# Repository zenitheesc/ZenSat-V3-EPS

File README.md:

<h1 align="center" style="color:white; background-color:black">ZenSat V3</h1>
<h4 align="center">Projeto de um CubeSat 2U para a competição Cube Design</h4>

<p align="center">

</p>

<p align="center">
    <a href="#environment-and-tools">Environment and Tools</a> •
    <a href="#steps-to-run-and-debug">Steps to run and debug</a> •
    <a href="#how-to-contribute">How to contribute?</a> •
</p>

## Environment and tools

`Add list of dependencies and software needed to run this project (if possible add the versions that were used in development).`

## Steps to run and debug

`A simple list of steps indicating how one can run and test the project.`

## How to contribute

`(optional, depends on the project) list of simple rules to help people work on the project.`

`Examples: How to format a pull request\n How to format an issue`

---

<p align="center">

</p>
<p align = "center">
<a href="zenith.eesc@gmail.com">zenith.eesc@gmail.com</a>
</p>

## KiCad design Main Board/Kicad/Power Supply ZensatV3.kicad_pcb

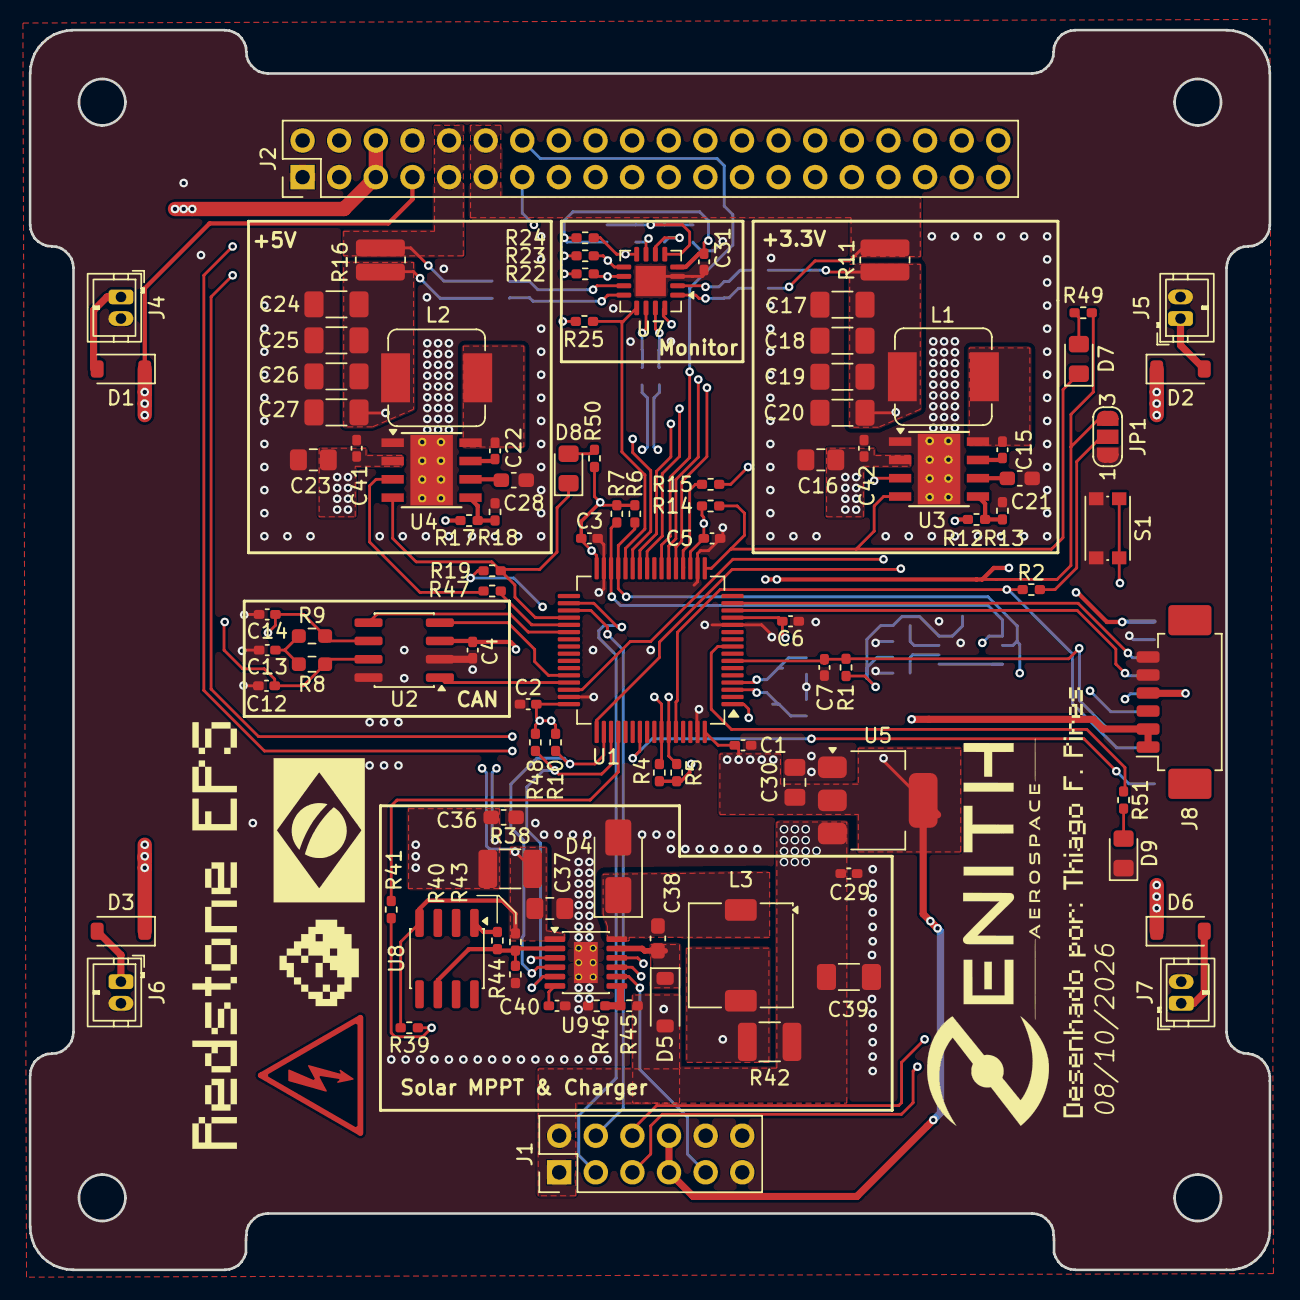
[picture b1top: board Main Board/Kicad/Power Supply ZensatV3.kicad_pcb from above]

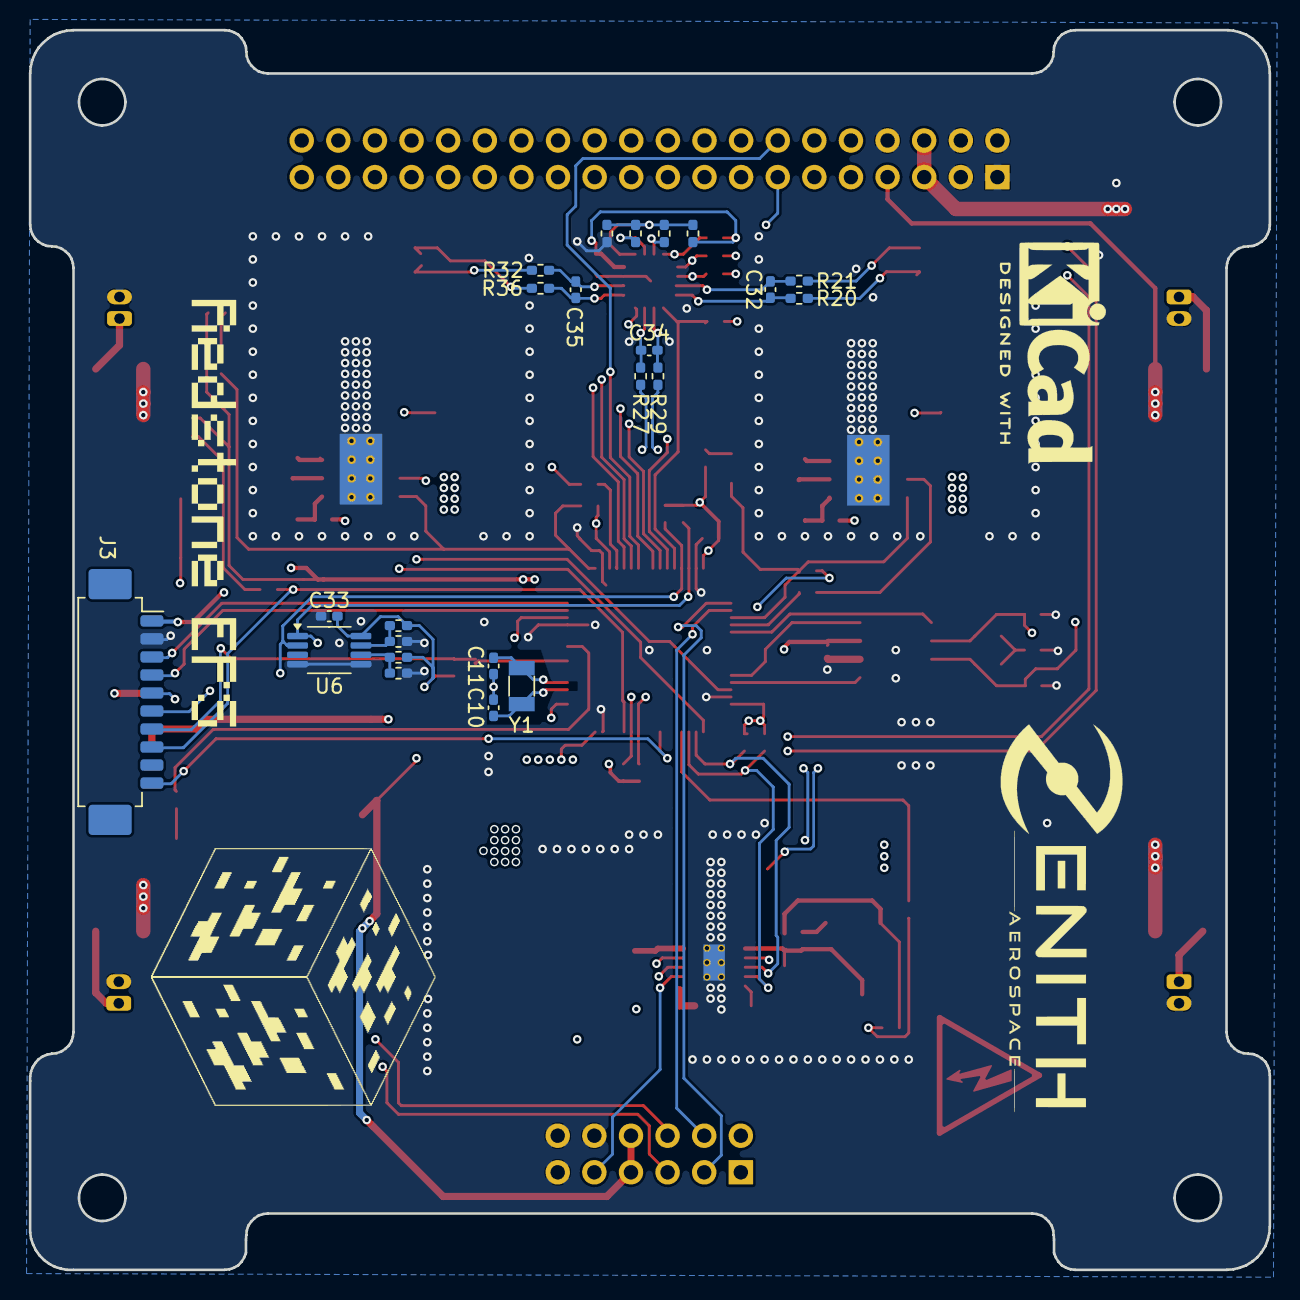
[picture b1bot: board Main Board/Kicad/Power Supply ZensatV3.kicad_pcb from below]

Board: 4 copper layers, 86.0 x 86.0 mm, 122 parts (23 on the bottom side), 81 nets.

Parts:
C1, C2, C3, C4, C5, C6, C15, C22, C33: 100nF; C_0402_1005Metric_Pad0.74x0.62mm_HandSolder
C7: 1u; C_0402_1005Metric_Pad0.74x0.62mm_HandSolder
C10, C11: 7p; C_0402_1005Metric_Pad0.74x0.62mm_HandSolder
C12, C14: 33p; C_0402_1005Metric_Pad0.74x0.62mm_HandSolder
C13: 4n7; C_0402_1005Metric_Pad0.74x0.62mm_HandSolder
C16, C23, C37: 10uF; C_0805_2012Metric_Pad1.18x1.45mm_HandSolder
C17, C18, C19, C20, C24, C25, C26, C27: 22uF; C_1206_3216Metric_Pad1.33x1.80mm_HandSolder
C21, C28, C36: 1uF; C_0603_1608Metric_Pad1.08x0.95mm_HandSolder
C29: 100nF 25V; C_0402_1005Metric_Pad0.74x0.62mm_HandSolder
C30: 10uF 10V; C_0805_2012Metric_Pad1.18x1.45mm_HandSolder
C31, C32, C34, C35: 100nF 10V; C_0402_1005Metric_Pad0.74x0.62mm_HandSolder
C38: 1uF 50V; C_0603_1608Metric_Pad1.08x0.95mm_HandSolder
C39: 10uF 25V; C_1206_3216Metric_Pad1.33x1.80mm_HandSolder
C40: 680nF; C_0402_1005Metric_Pad0.74x0.62mm_HandSolder
C41, C42: 220nF; C_0402_1005Metric_Pad0.74x0.62mm_HandSolder
D1, D2, D3, D5, D6: 1N5819HW; D_SOD-123
D4: SS34; D_SMA
D7, D8: LEDG; LED_0805_2012Metric_Pad1.15x1.40mm_HandSolder
D9: LEDR; LED_0805_2012Metric_Pad1.15x1.40mm_HandSolder
J1: BatBus; PinHeader_2x06_P2.54mm_Vertical
J2: ZenBus; PinHeader_2x20_P2.54mm_Vertical
J3: Programmer; Molex_PicoBlade_53261-1071_1x10-1MP_P1.25mm_Horizontal
J4, J5, J6, J7: Conn_01x02_Pin; JST_ZH_B2B-ZR_1x02_P1.50mm_Vertical
J8: External Power; Molex_PicoBlade_53261-0671_1x06-1MP_P1.25mm_Horizontal
JP1: BOOT; SolderJumper-3_P1.3mm_Open_RoundedPad1.0x1.5mm_NumberLabels
L1: 6,8uH; L_Sumida_CDMC6D28_7.25x6.5mm
L2: 8uH; L_Sumida_CDMC6D28_7.25x6.5mm
L3: 47uH; L_TDK_SLF7032
R1, R2, R4, R5, R10, R14, R19, R22, R23, R24, R25, R48, R51: 10k; R_0402_1005Metric_Pad0.72x0.64mm_HandSolder
R6, R7: 4k7; R_0402_1005Metric_Pad0.72x0.64mm_HandSolder
R8, R9: 60; R_0603_1608Metric_Pad0.98x0.95mm_HandSolder
R11, R16: R05; R_0612_1632Metric_Pad1.18x3.40mm_HandSolder
R12, R17: 100k; R_0402_1005Metric_Pad0.72x0.64mm_HandSolder
R13: 43,2k; R_0402_1005Metric_Pad0.72x0.64mm_HandSolder
R15, R43, R47: 1k; R_0402_1005Metric_Pad0.72x0.64mm_HandSolder
R18: 14,9k; R_0402_1005Metric_Pad0.72x0.64mm_HandSolder
R20, R21, R27, R29, R32, R36: 10R; R_0402_1005Metric_Pad0.72x0.64mm_HandSolder
R26, R28, R30, R31, R33, R34, R35, R37, R39, R41: 0R; R_0402_1005Metric_Pad0.72x0.64mm_HandSolder
R38, R42: 0R33; R_1210_3225Metric_Pad1.30x2.65mm_HandSolder
R40: 233k; R_0402_1005Metric_Pad0.72x0.64mm_HandSolder
R44: 25,2k; R_0402_1005Metric_Pad0.72x0.64mm_HandSolder
R45: 626k; R_0402_1005Metric_Pad0.72x0.64mm_HandSolder
R46: 412k; R_0402_1005Metric_Pad0.72x0.64mm_HandSolder
R49, R50: 470R; R_0402_1005Metric_Pad0.72x0.64mm_HandSolder
S1: RST; SW_Push_1P1T_NO_CK_KMR2
U1: STM32L476RGTx; LQFP-64_10x10mm_P0.5mm
U2: SN65HVD233; SOIC-8_3.9x4.9mm_P1.27mm
U3, U4: LMR33630ADDA; Texas_HSOP-8-1EP_3.9x4.9mm_P1.27mm_ThermalVias
U5: AMS1117-3.3; SOT-223-3_TabPin2
U6: LM75B; Texas_S-PDSO-G8_3x3mm_P0.65mm
U7: INA3221; Texas_RGV0016A_VQFN-16-1EP_4x4mm_P0.65mm_EP2.1x2.1mm
U8: LM234DT; SOIC-8_3.9x4.9mm_P1.27mm
U9: LT3652IMSE; MSOP-12-1EP_3x4.039mm_P0.65mm_EP1.651x2.845mm_ThermalVias
Y1: 32,768k; Crystal_SMD_3215-2Pin_3.2x1.5mm

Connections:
+3.3VP: C1.2, C2.2, C3.2, C4.2, C5.2, C6.2, C30.2, C31.2, C33.2, J1.7, J1.8, J3.1, JP1.3 (B), R1.1, R4.1, R5.1, R6.1, R7.1, R10.1, R14.1, R19.1, R22.2, R23.2, R24.2, R25.2, R26.1, R30.1, R31.1, R48.1, R49.1, R50.1, U1.1 (VBAT), U1.13 (VDDA), U1.19 (VDD), U1.32 (VDD), U1.48 (VDDUSB), U1.64 (VDD), U2.3 (VCC), U5.2 (VO), U6.8 (+Vs), U7.4 (VS), U7.16 (VPU)
+3V3: J2.11, J2.12, R11.2, R36.2
+3V3_Sense: C17.2, C18.2, C19.2, C20.2, L1.2, R11.1, R12.1, R32.2
+5V: J2.9, J2.10, R16.2, R21.2
+5V_Sense: C24.2, C25.2, C26.2, C27.2, L2.2, R16.1, R17.1, R20.2
/+3V3_En: R15.1, U1.20 (PA4)
/+3V3_PG: D7.1 (K), R14.2, U1.17 (PA3), U3.4 (PG)
/+5V_En: R47.1, U1.37 (PC6)
/+5V_PG: D8.1 (K), R19.2, U1.36 (PB15), U4.4 (PG)
/BOOT0: J3.8, R2.1, U1.60 (BOOT0)
/BUS_CAN+: C12.2, J2.16, R8.1, U2.7 (CANH)
/BUS_CAN-: C14.1, J2.18, R9.2, U2.6 (CANL)
/BUS_I2C_SCL: J2.19, R4.2, U1.58 (PB6)
/BUS_I2C_SDA: J2.17, R5.2, U1.59 (PB7)
/CAN_Rx: U1.44 (PA11), U2.4 (R)
/CAN_Tx: U1.45 (PA12), U2.1 (D)
/CRITICAL: R23.1, U1.26 (PB0), U7.9 (CRITICAL)
/DebugLed: R51.1, U1.9 (PC1)
/Deploy: J1.4, U1.35 (PB14)
/Heater: J1.3, U1.34 (PB13)
/I2C2_SCL: J1.5, R6.2, R35.1, U1.29 (PB10), U6.2 (SCL), U7.6 (SCL)
/I2C2_SDA: J1.6, R7.2, R33.1, U1.30 (PB11), U6.1 (SDA), U7.7 (SDA)
/LBK: U1.38 (PC7), U2.5 (LBK)
/NRST: C7.1, J3.7, R1.2, S1.1, U1.7 (NRST)
/NTC: J1.9, U9.8 (NTC)
/OSC32_IN: C10.1, U1.3 (PC14), Y1.2
/OSC32_OUT: C11.2, U1.4 (PC15), Y1.1
/PV: R22.1, U1.25 (PC5), U7.10 (PV)
/SPI1_MISO: J2.13, U1.22 (PA6)
/SPI1_MOSI: J2.14, U1.23 (PA7)
/SPI1_SCK: J2.15, U1.21 (PA5)
/SWCLK: J3.5, U1.49 (PA14)
/SWDIO: J3.6, U1.46 (PA13)
/SWO: J3.10, U1.55 (PB3)
/TC: R25.1, U1.28 (PB2), U7.13 (TC)
/UART_Rx: J3.3, U1.15 (PA1)
/UART_Tx: J3.4, U1.14 (PA0)
/WARNING: R24.1, U1.27 (PB1), U7.8 (WARNING)
/~CHRG: R10.2, U1.50 (PA15), U9.4 (~CHRG)
/~FAULT: R48.2, U1.51 (PC10), U9.5 (~FAULT)
/~SHDN: R41.1, U1.52 (PC11)
BAT+: C16.2, C23.2, C29.2, C39.1, C41.2, C42.2, D5.2 (A), J1.1, J1.2, J2.5, J2.6, J8.1, J8.2, R42.2, R45.2, U3.2 (VIN), U4.2 (VIN), U5.3 (VI), U9.9 (BAT)
GND: C1.1, C2.1, C3.1, C4.1, C5.1, C6.1, C7.2, C10.2, C11.1, C12.1, C13.2, C14.2, C16.1, C17.1, C18.1, C19.1, C20.1, C21.1, C23.1, C24.1, C25.1, C26.1, C27.1, C28.1, C29.1, C30.1, C31.1, C33.1, C36.1, C37.2, C39.2, C40.2, C41.1, C42.1, D4.2 (A), D9.1 (K), J1.10, J1.11, J1.12, J2.1, J2.2, J2.3, J2.4, J2.8, J3.2, J4.2, J5.2, J6.2, J7.2, J8.5, J8.6, JP1.1 (A), R13.2, R18.2, R28.1, R34.1, R37.1, R44.1, R46.1, S1.2, U1.12 (VSSA), U1.18 (VSS), U1.31 (VSS), U1.47 (VSS), U1.63 (VSS), U2.2 (GND), U2.8 (Rs), U3.1 (GND), U3.9 (GND), U4.1 (GND), U4.9 (GND), U5.1 (GND), U6.4 (GND), U6.5 (A2), U7.3 (GND), U7.17 (EP), U9.13 (GND)
unnamed: C13.1, R8.2, R9.1
unnamed: D1.2 (A), J4.1
unnamed: D2.2 (A), J5.1
unnamed: D3.2 (A), J6.1
unnamed: C38.1, D4.1 (K), L3.1, U9.12 (SW)
unnamed: C38.2, D5.1 (K), U9.11 (BOOST)
unnamed: D6.2 (A), J7.1
unnamed: D7.2 (A), R49.2
unnamed: D8.2 (A), R50.2
unnamed: D9.2 (A), R51.2
unnamed: JP1.2 (C), R2.2
unnamed: R43.2, U8.1
unnamed: C15.1, U3.7 (BOOT)
unnamed: R15.2, U3.3 (EN)
unnamed: R12.2, R13.1, U3.5 (FB)
unnamed: C15.2, L1.1, U3.8 (SW)
unnamed: C21.2, U3.6 (VCC)
unnamed: C22.1, U4.7 (BOOT)
unnamed: R47.2, U4.3 (EN)
unnamed: R17.2, R18.1, U4.5 (FB)
unnamed: C22.2, L2.1, U4.8 (SW)
unnamed: C28.2, U4.6 (VCC)
unnamed: R26.2, R28.2, U6.7 (A0)
unnamed: R31.2, R34.2, U6.6 (A1)
unnamed: R30.2, R33.2, R35.2, R37.2, U7.5 (A0)
unnamed: C32.1, R20.1, U7.12 (IN+1)
unnamed: C34.1, R27.1, U7.15 (IN+2)
unnamed: C35.1, R32.1, U7.2 (IN+3)
unnamed: C32.2, R21.1, U7.11 (IN-1)
unnamed: C34.2, R29.1, U7.14 (IN-2)
unnamed: C35.2, R36.1, U7.1 (IN-3)
unnamed: L3.2, R42.1, U9.10 (SENSE)
unnamed: C40.1, U9.6 (TIMER)
unnamed: R45.1, R46.2, U9.7 (V_{FB})
unnamed: R40.1, R43.1, R44.2, U8.6, U9.2 (V_{IN_REG})
unnamed: R39.1, R41.2, U9.3 (~SHDN)
SOL+: C36.2, D1.1 (K), D2.1 (K), D3.1 (K), D6.1 (K), J2.7, J8.4, R27.2, R38.1
SOL_Sense-: C37.1, R29.2, R38.2, R39.2, R40.2, U8.4, U9.1 (V_{IN})

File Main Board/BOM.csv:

"Reference","Qty","Value","DNP","Exclude from BOM","Exclude from Board","Footprint"
"C1,C2,C3,C4,C5,C6,C15,C22,C33","9","100nF","","","","Capacitor_SMD:C_0402_1005Metric_Pad0.74x0.62mm_HandSolder"
"C7","1","1u","","","","Capacitor_SMD:C_0402_1005Metric_Pad0.74x0.62mm_HandSolder"
"C10,C11","2","7p","","","","Capacitor_SMD:C_0402_1005Metric_Pad0.74x0.62mm_HandSolder"
"C12,C14","2","33p","","","","Capacitor_SMD:C_0402_1005Metric_Pad0.74x0.62mm_HandSolder"
"C13","1","4n7","","","","Capacitor_SMD:C_0402_1005Metric_Pad0.74x0.62mm_HandSolder"
"C16,C23,C37","3","10uF","","","","Capacitor_SMD:C_0805_2012Metric_Pad1.18x1.45mm_HandSolder"
"C17,C18,C19,C20,C24,C25,C26,C27","8","22uF","","","","Capacitor_SMD:C_1206_3216Metric_Pad1.33x1.80mm_HandSolder"
"C21,C28,C36","3","1uF","","","","Capacitor_SMD:C_0603_1608Metric_Pad1.08x0.95mm_HandSolder"
"C29","1","100nF 25V","","","","Capacitor_SMD:C_0402_1005Metric_Pad0.74x0.62mm_HandSolder"
"C30","1","10uF 10V","","","","Capacitor_SMD:C_0805_2012Metric_Pad1.18x1.45mm_HandSolder"
"C31,C32,C34,C35","4","100nF 10V","","","","Capacitor_SMD:C_0402_1005Metric_Pad0.74x0.62mm_HandSolder"
"C38","1","1uF 50V","","","","Capacitor_SMD:C_0603_1608Metric_Pad1.08x0.95mm_HandSolder"
"C39","1","10uF 25V","","","","Capacitor_SMD:C_1206_3216Metric_Pad1.33x1.80mm_HandSolder"
"C40","1","680nF","","","","Capacitor_SMD:C_0402_1005Metric_Pad0.74x0.62mm_HandSolder"
"C41,C42","2","220nF","","","","Capacitor_SMD:C_0402_1005Metric_Pad0.74x0.62mm_HandSolder"
"D1,D2,D3,D5,D6","5","1N5819HW","","","","Diode_SMD:D_SOD-123"
"D4","1","SS34","","","","Diode_SMD:D_SMA"
"D7,D8","2","LEDG","","","","LED_SMD:LED_0805_2012Metric_Pad1.15x1.40mm_HandSolder"
"D9","1","LEDR","","","","LED_SMD:LED_0805_2012Metric_Pad1.15x1.40mm_HandSolder"
"J1","1","BatBus","","","","Connector_PinHeader_2.54mm:PinHeader_2x06_P2.54mm_Vertical"
"J2","1","ZenBus","","","","Connector_PinHeader_2.54mm:PinHeader_2x20_P2.54mm_Vertical"
"J3","1","Programmer","","","","Connector_Molex:Molex_PicoBlade_53261-1071_1x10-1MP_P1.25mm_Horizontal"
"J4,J5,J6,J7","4","Conn_01x02_Pin","","","","Connector_JST:JST_ZH_B2B-ZR_1x02_P1.50mm_Vertical"
"J8","1","External Power","","","","Connector_Molex:Molex_PicoBlade_53261-0671_1x06-1MP_P1.25mm_Horizontal"
"JP1","1","BOOT","","","","Jumper:SolderJumper-3_P1.3mm_Open_RoundedPad1.0x1.5mm_NumberLabels"
"L1","1","6,8uH","","","","Inductor_SMD:L_Sumida_CDMC6D28_7.25x6.5mm"
"L2","1","8uH","","","","Inductor_SMD:L_Sumida_CDMC6D28_7.25x6.5mm"
"L3","1","47uH","","","","Inductor_SMD:L_TDK_SLF7032"
"R1,R2,R4,R5,R10,R14,R19,R22,R23,R24,R25,R48,R51","13","10k","","","","Resistor_SMD:R_0402_1005Metric_Pad0.72x0.64mm_HandSolder"
"R6,R7","2","4k7","","","","Resistor_SMD:R_0402_1005Metric_Pad0.72x0.64mm_HandSolder"
"R8,R9","2","60","","","","Resistor_SMD:R_0603_1608Metric_Pad0.98x0.95mm_HandSolder"
"R11,R16","2","R05","","","","Resistor_SMD:R_0612_1632Metric_Pad1.18x3.40mm_HandSolder"
"R12,R17","2","100k","","","","Resistor_SMD:R_0402_1005Metric_Pad0.72x0.64mm_HandSolder"
"R13","1","43,2k","","","","Resistor_SMD:R_0402_1005Metric_Pad0.72x0.64mm_HandSolder"
"R15,R43,R47","3","1k","","","","Resistor_SMD:R_0402_1005Metric_Pad0.72x0.64mm_HandSolder"
"R18","1","14,9k","","","","Resistor_SMD:R_0402_1005Metric_Pad0.72x0.64mm_HandSolder"
"R28,R33,R34,R35,R37,R39,R41","7","0R","","","","Resistor_SMD:R_0402_1005Metric_Pad0.72x0.64mm_HandSolder"
"R38,R42","2","0R33","","","","Resistor_SMD:R_1210_3225Metric_Pad1.30x2.65mm_HandSolder"
"R40","1","233k","","","","Resistor_SMD:R_0402_1005Metric_Pad0.72x0.64mm_HandSolder"
"R44","1","25,2k","","","","Resistor_SMD:R_0402_1005Metric_Pad0.72x0.64mm_HandSolder"
"R45","1","626k","","","","Resistor_SMD:R_0402_1005Metric_Pad0.72x0.64mm_HandSolder"
"R46","1","412k","","","","Resistor_SMD:R_0402_1005Metric_Pad0.72x0.64mm_HandSolder"
"R49,R50","2","470R","","","","Resistor_SMD:R_0402_1005Metric_Pad0.72x0.64mm_HandSolder"
"S1","1","RST","","","","Button_Switch_SMD:SW_Push_1P1T_NO_CK_KMR2"
"U1","1","STM32L476RGTx","","","","Package_QFP:LQFP-64_10x10mm_P0.5mm"
"U2","1","SN65HVD233","","","","Package_SO:SOIC-8_3.9x4.9mm_P1.27mm"
"U3,U4","2","LMR33630ADDA","","","","Package_SO:Texas_HSOP-8-1EP_3.9x4.9mm_P1.27mm_ThermalVias"
"U5","1","AMS1117-3.3","","","","Package_TO_SOT_SMD:SOT-223-3_TabPin2"
"U6","1","LM75B","","","","Package_SO:Texas_S-PDSO-G8_3x3mm_P0.65mm"
"U7","1","INA3221","","","","Package_DFN_QFN:Texas_RGV0016A_VQFN-16-1EP_4x4mm_P0.65mm_EP2.1x2.1mm"
"U8","1","LM234DT","","","","Package_SO:SOIC-8_3.9x4.9mm_P1.27mm"
"U9","1","LT3652IMSE","","","","Package_SO:MSOP-12-1EP_3x4.039mm_P0.65mm_EP1.651x2.845mm_ThermalVias"
"Y1","1","32,768k","","","","Crystal:Crystal_SMD_3215-2Pin_3.2x1.5mm"

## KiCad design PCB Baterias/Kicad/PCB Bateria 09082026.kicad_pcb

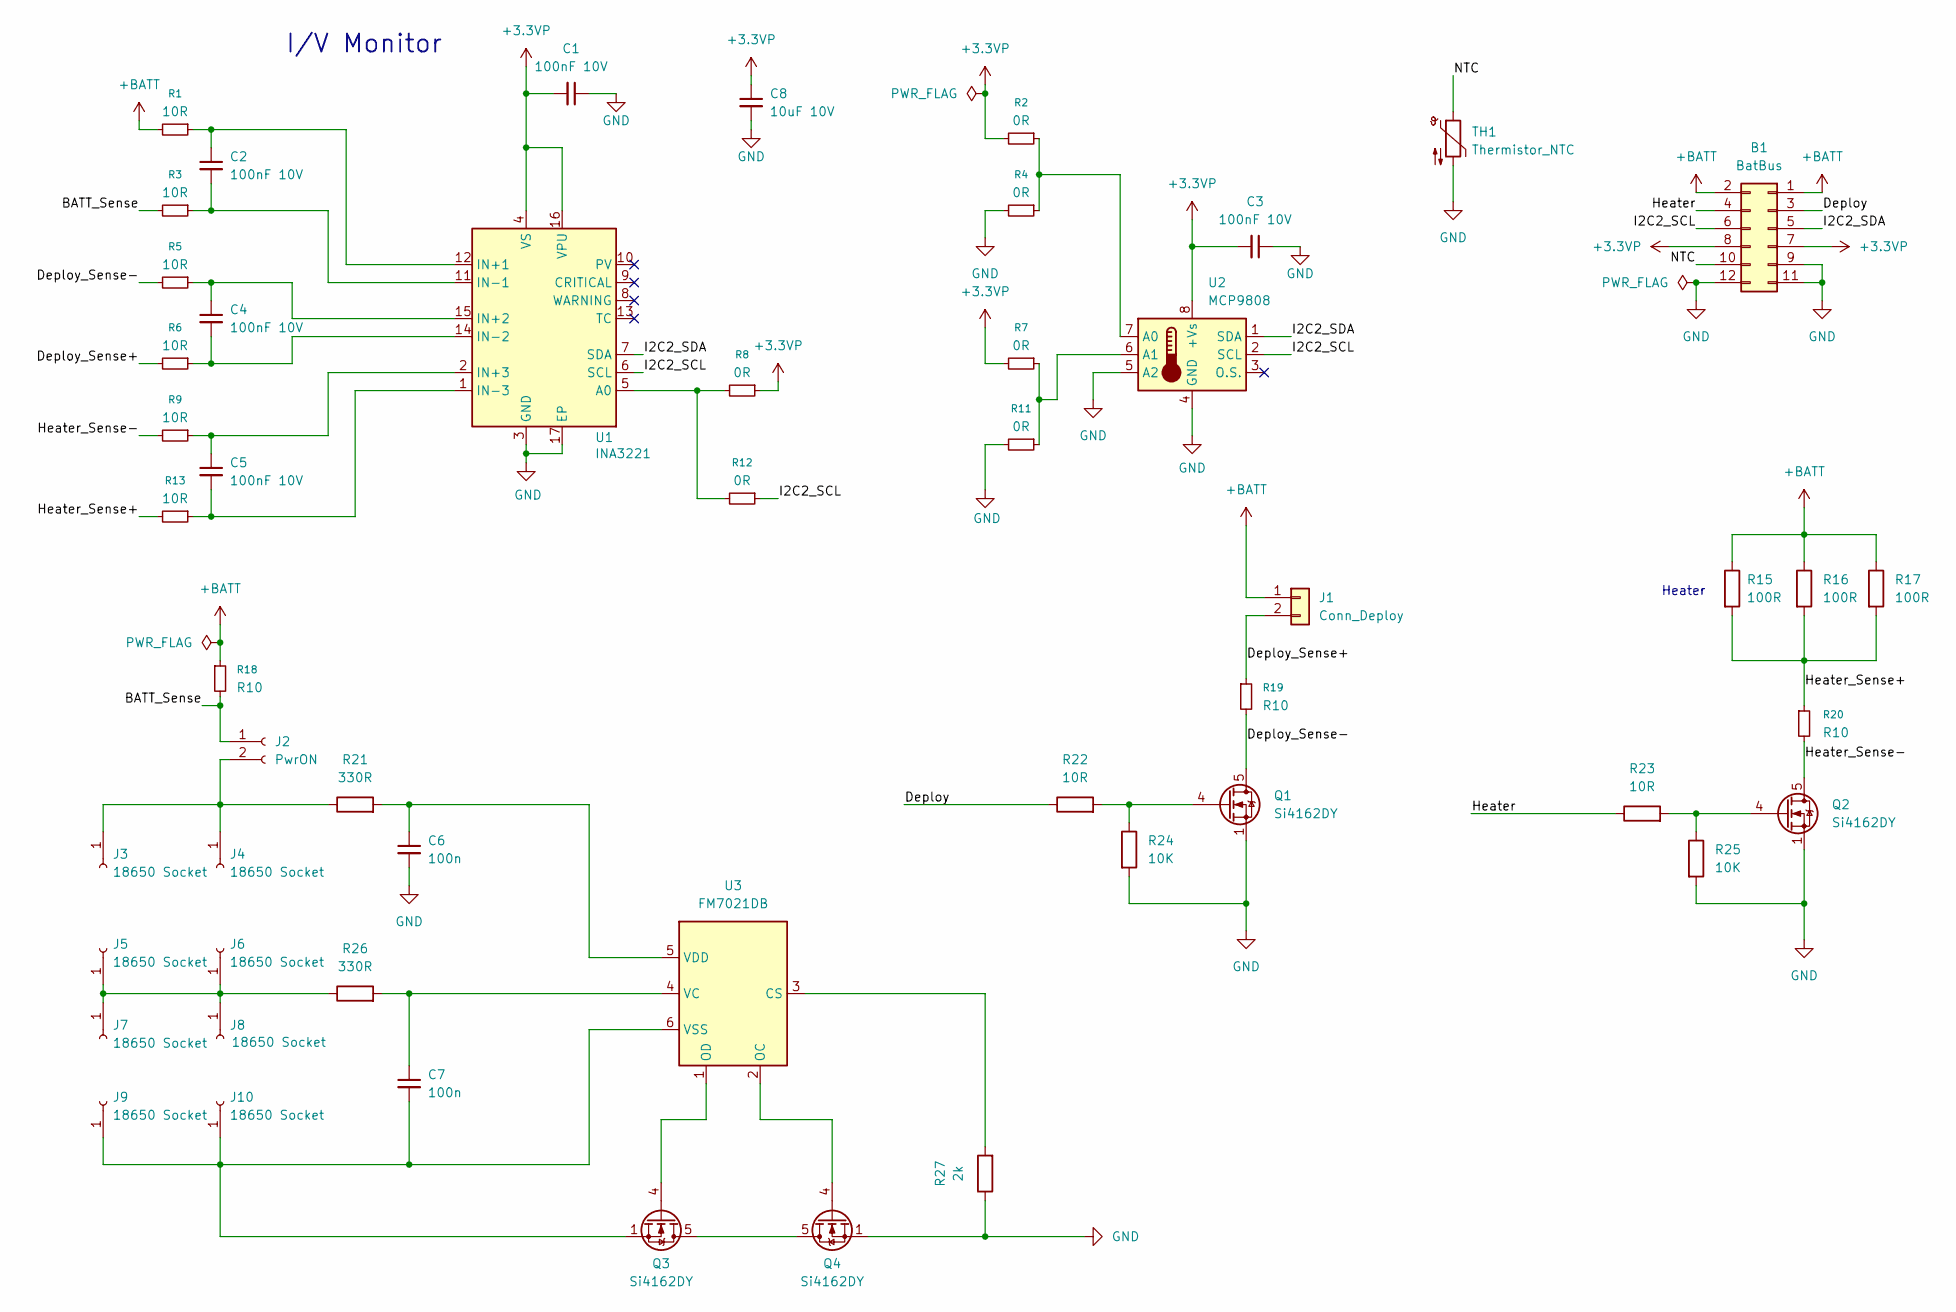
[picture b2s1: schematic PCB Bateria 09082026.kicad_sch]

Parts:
B1: BatBus; PinHeader_2x06_P2.54mm_Vertical_SMD
C1, C2, C3, C4, C5: 100nF 10V; C_0402_1005Metric_Pad0.74x0.62mm_HandSolder
C6, C7: 100n; C_0402_1005Metric_Pad0.74x0.62mm_HandSolder
C8: 10uF 10V; C_0805_2012Metric_Pad1.18x1.45mm_HandSolder
J1: Conn_Deploy; Molex_KK-254_AE-6410-02A_1x02_P2.54mm_Vertical
J2: PwrON; PinHeader_1x02_P2.54mm_Vertical
J3, J4, J5, J6, J7, J8, J9, J10: 18650 Socket; BatteryClip_Keystone_54_D16-19mm
Q1, Q2, Q3, Q4: Si4162DY; SOIC-8_3.9x4.9mm_P1.27mm
R1, R3, R5, R6, R9, R13, R22, R23: 10R; R_0402_1005Metric_Pad0.72x0.64mm_HandSolder
R2, R4, R7, R8, R11, R12: 0R; R_0402_1005Metric_Pad0.72x0.64mm_HandSolder
R15, R16, R17: 100R; R_Axial_DIN0516_L15.5mm_D5.0mm_P30.48mm_Horizontal
R18, R19, R20: R10; R_1206_3216Metric_Pad1.30x1.75mm_HandSolder
R21, R26: 330R; R_0402_1005Metric_Pad0.72x0.64mm_HandSolder
R24, R25: 10K; R_0402_1005Metric_Pad0.72x0.64mm_HandSolder
R27: 2k; R_0402_1005Metric_Pad0.72x0.64mm_HandSolder
TH1: Thermistor_NTC; R_Axial_DIN0204_L3.6mm_D1.6mm_P1.90mm_Vertical
U1: INA3221; Texas_RGV0016A_VQFN-16-1EP_4x4mm_P0.65mm_EP2.1x2.1mm
U2: MCP9808; MSOP-8_3x3mm_P0.65mm
U3: FM7021DB; SOT-23-6

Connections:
+3.3VP: B1.7, B1.8, C1.2, C3.2, C8.1, R2.2, R7.2, R8.1, U1.4 (VS), U1.16 (VPU), U2.8 (+Vs)
+BATT: B1.1, B1.2, J1.1, R1.2, R15.1, R16.1, R17.1, R18.1
/BATT_Sense: J2.1, R3.2, R18.2
/Deploy: B1.3, R22.1
/Deploy_Sense+: J1.2, R6.2, R19.1
/Deploy_Sense-: Q1.5 (D), Q1.6 (D), Q1.7 (D), Q1.8 (D), R5.2, R19.2
/Heater: B1.4, R23.1
/Heater_Sense+: R13.2, R15.2, R16.2, R17.2, R20.1
/Heater_Sense-: Q2.5 (D), Q2.6 (D), Q2.7 (D), Q2.8 (D), R9.2, R20.2
/I2C2_SCL: B1.6, R12.1, U1.6 (SCL), U2.2 (SCL)
/I2C2_SDA: B1.5, U1.7 (SDA), U2.1 (SDA)
/NTC: B1.10, TH1.1
GND: B1.9, B1.11, B1.12, C1.1, C3.1, C6.2, C8.2, Q1.1 (S), Q1.2 (S), Q1.3 (S), Q2.1 (S), Q2.2 (S), Q2.3 (S), Q4.1 (S), Q4.2 (S), Q4.3 (S), R4.2, R11.2, R24.2, R25.2, R27.1, TH1.2, U1.3 (GND), U1.17 (EP), U2.4 (GND), U2.5 (A2)
unnamed: J2.2, J3.1 (Pin_1_1), J4.1 (Pin_1_1), R21.1
unnamed: J5.1 (Pin_1_1), J6.1 (Pin_1_1), J7.1 (Pin_1_1), J8.1 (Pin_1_1), R26.1
unnamed: C7.2, J9.1 (Pin_1_1), J10.1 (Pin_1_1), Q3.1 (S), Q3.2 (S), Q3.3 (S), U3.6 (VSS)
unnamed: Q1.4 (G), R22.2, R24.1
unnamed: Q2.4 (G), R23.2, R25.1
unnamed: Q3.5 (D), Q3.6 (D), Q3.7 (D), Q3.8 (D), Q4.5 (D), Q4.6 (D), Q4.7 (D), Q4.8 (D)
unnamed: Q3.4 (G), U3.1 (OD)
unnamed: Q4.4 (G), U3.2 (OC)
unnamed: R8.2, R12.2, U1.5 (A0)
unnamed: C2.1, R1.1, U1.12 (IN+1)
unnamed: C4.1, R5.1, U1.15 (IN+2)
unnamed: C5.1, R9.1, U1.2 (IN+3)
unnamed: C2.2, R3.1, U1.11 (IN-1)
unnamed: C4.2, R6.1, U1.14 (IN-2)
unnamed: C5.2, R13.1, U1.1 (IN-3)
unnamed: R2.1, R4.1, U2.7 (A0)
unnamed: R7.1, R11.1, U2.6 (A1)
unnamed: R27.2, U3.3 (CS)
unnamed: C7.1, R26.2, U3.4 (VC)
unnamed: C6.1, R21.2, U3.5 (VDD)

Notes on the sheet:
Heater
I/V Monitor

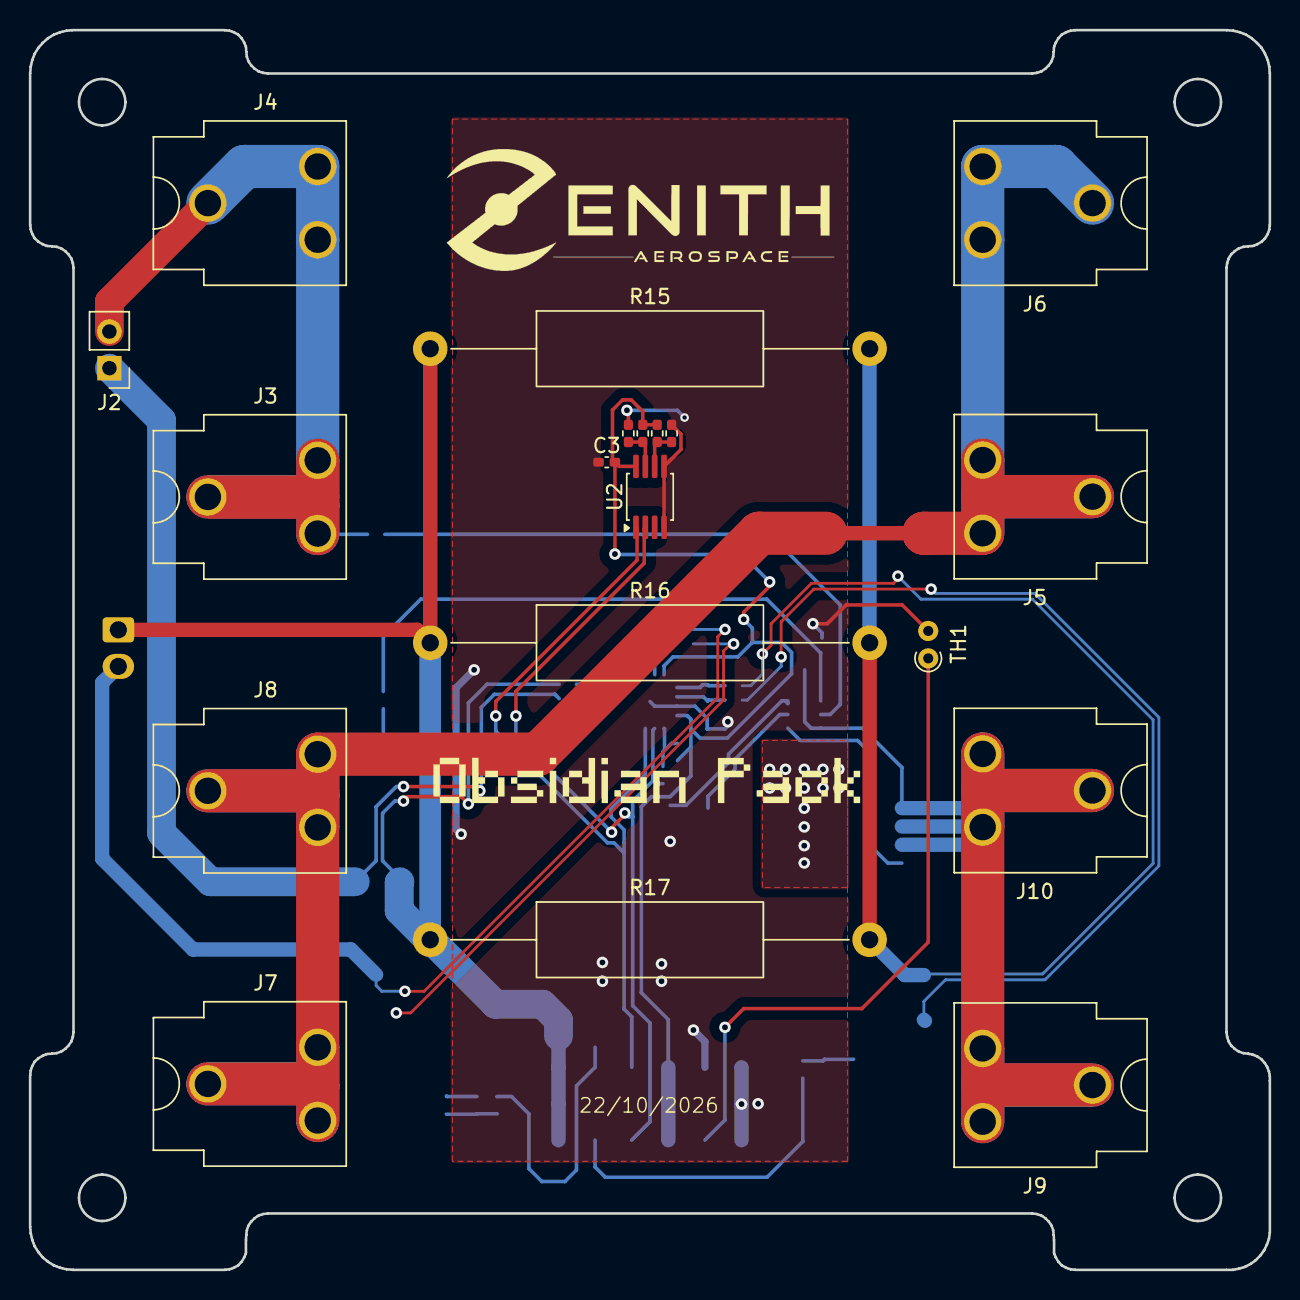
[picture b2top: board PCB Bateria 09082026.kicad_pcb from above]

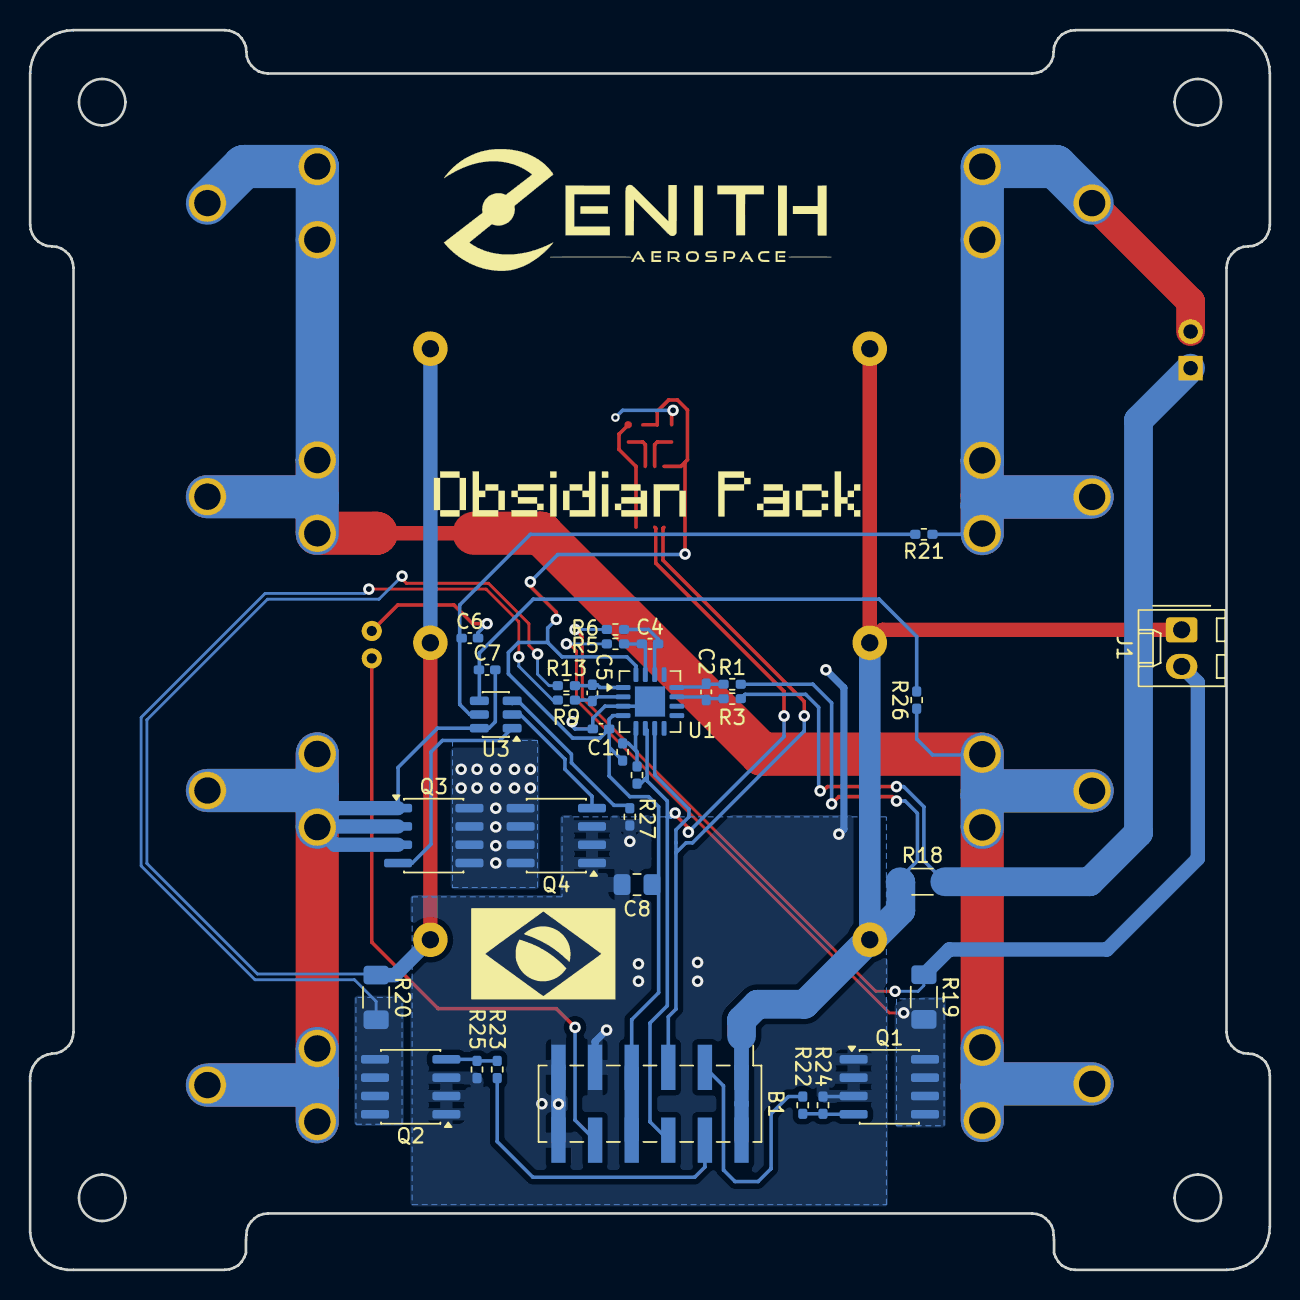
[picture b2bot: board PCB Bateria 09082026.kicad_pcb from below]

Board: 4 copper layers, 86.0 x 86.0 mm, 52 parts (33 on the bottom side), 33 nets.

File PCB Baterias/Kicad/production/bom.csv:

Designator,Footprint,Quantity,Value,LCSC Part #
B1,PinHeader_2x06_P2.54mm_Vertical_SMD,1,BatBus,
"C1, C2, C3, C4, C5",0402,5,100nF 10V,
"C6, C7",0402,2,100n,
C8,0805,1,10uF 10V,
J1,Molex_KK-254_AE-6410-02A_1x02_P2.54mm_Vertical,1,Conn_Deploy,
"J10, J3, J4, J5, J6, J7, J8, J9",BatteryClip_Keystone_54_D16-19mm,8,18650 Socket,
J2,PinHeader_1x02_P2.54mm_Vertical,1,PwrON,
"Q1, Q2, Q3, Q4",SOIC-8_3.9x4.9mm_P1.27mm,4,Si4162DY,
R12,0402,1,0R,
"R15, R16, R17",R_Axial_DIN0516_L15.5mm_D5.0mm_P30.48mm_Horizontal,3,100R,
"R21, R26",0402,2,330R,
"R22, R23",0402,2,10R,
"R24, R25",0402,2,10K,
R27,0402,1,2k,
TH1,R_Axial_DIN0204_L3.6mm_D1.6mm_P1.90mm_Vertical,1,Thermistor_NTC,
U1,Texas_RGV0016A_VQFN-16-1EP_4x4mm_P0.65mm_EP2.1x2.1mm,1,INA3221,
U2,MSOP-8_3x3mm_P0.65mm,1,MCP9808,
U3,SOT-23-6,1,FM7021DB,

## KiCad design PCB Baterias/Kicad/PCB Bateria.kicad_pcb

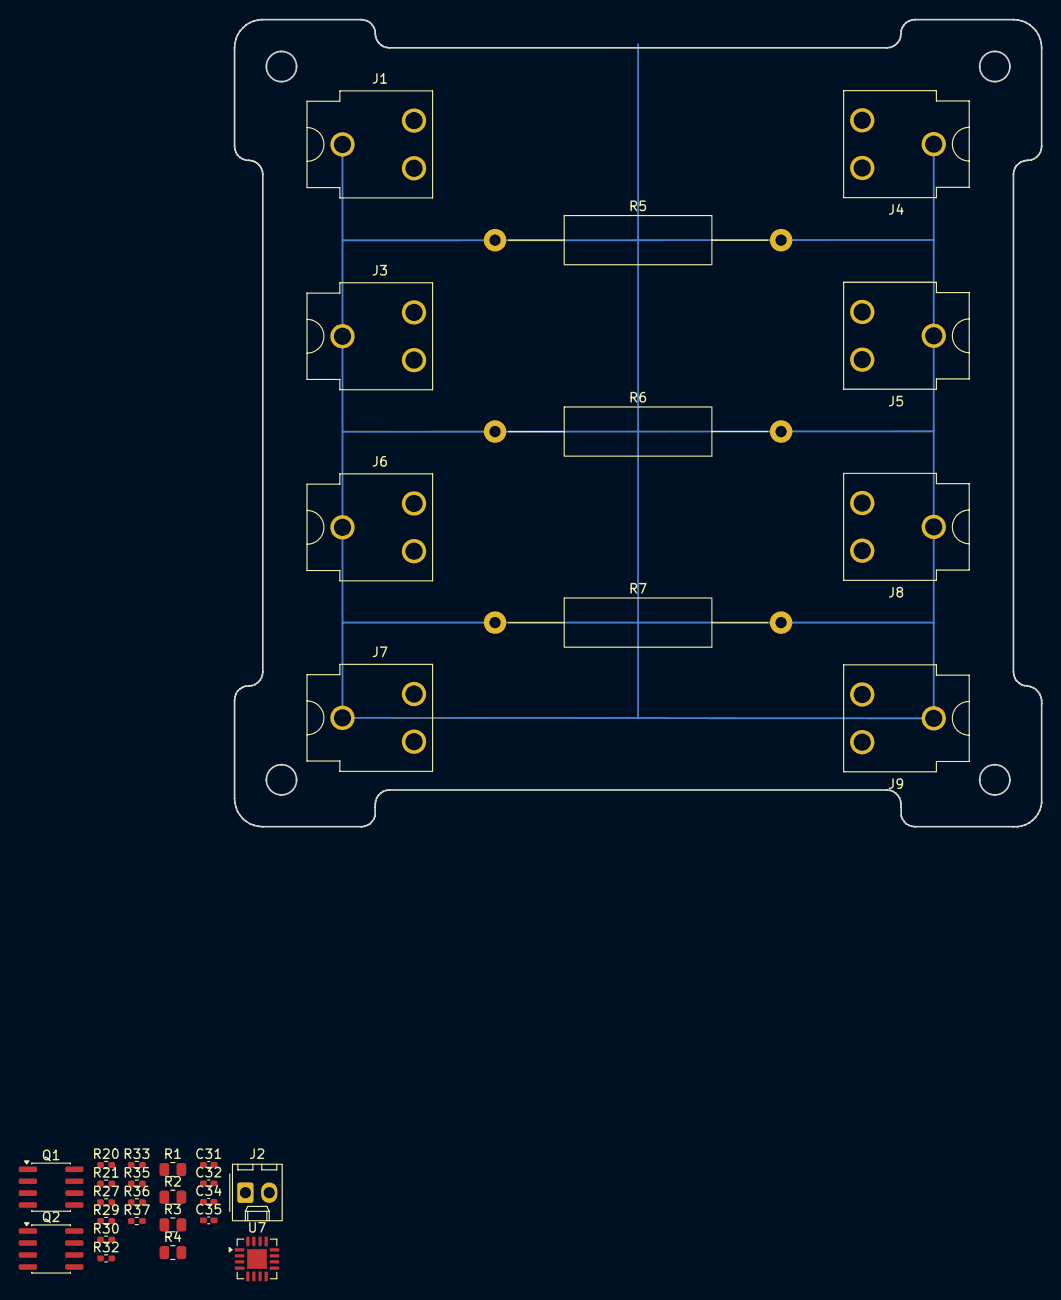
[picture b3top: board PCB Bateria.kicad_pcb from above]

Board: 2 copper layers, 86.0 x 86.0 mm, 34 parts (1 on the bottom side), 19 nets, no tracks yet.

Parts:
B1: BatBus; PinHeader_2x06_P2.54mm_Vertical_SMD
C31, C32, C34, C35: 100nF 10V; C_0402_1005Metric_Pad0.74x0.62mm_HandSolder
J1, J3, J4, J5, J6, J7, J8, J9: Conn_01x01_Socket; BatteryClip_Keystone_54_D16-19mm
J2: Conn_01x02; Molex_KK-254_AE-6410-02A_1x02_P2.54mm_Vertical
Q1, Q2: Si4162DY; SOIC-8_3.9x4.9mm_P1.27mm
R1, R3: 10R; R_0805_2012Metric
R2, R4: 10K; R_0805_2012Metric
R5, R6, R7: 100R; R_Axial_DIN0516_L15.5mm_D5.0mm_P30.48mm_Horizontal
R20, R21, R27, R29, R32, R36: 10R; R_0402_1005Metric_Pad0.72x0.64mm_HandSolder
R30, R33, R35, R37: 0R; R_0402_1005Metric_Pad0.72x0.64mm_HandSolder
U7: INA3221; Texas_RGV0016A_VQFN-16-1EP_4x4mm_P0.65mm_EP2.1x2.1mm

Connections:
+3.3V: B1.7, B1.8, R36.2
+3.3VP: C31.2, R30.1, U7.4 (VS), U7.16 (VPU)
+BATT: B1.1, B1.2, J1.1 (Pin_1_1), J2.1, J3.1 (Pin_1_1), R5.1, R6.1, R7.1
/DEPLOY: R1.1, R3.1
/SCL: R35.1, U7.6 (SCL)
/SDA: R33.1, U7.7 (SDA)
GND: B1.10, B1.11, B1.12, C31.1, J8.1 (Pin_1_1), J9.1 (Pin_1_1), Q1.1 (S), Q1.2 (S), Q1.3 (S), Q2.1 (S), Q2.2 (S), Q2.3 (S), R2.2, R4.2, R37.1, U7.3 (GND), U7.17 (EP)
unnamed: J2.2, Q1.5 (D), Q1.6 (D), Q1.7 (D), Q1.8 (D)
unnamed: J4.1 (Pin_1_1), J5.1 (Pin_1_1), J6.1 (Pin_1_1), J7.1 (Pin_1_1)
unnamed: Q1.4 (G), R1.2, R2.1
unnamed: Q2.5 (D), Q2.6 (D), Q2.7 (D), Q2.8 (D), R5.2, R6.2, R7.2
unnamed: Q2.4 (G), R3.2, R4.1
unnamed: R30.2, R33.2, R35.2, R37.2, U7.5 (A0)
unnamed: C32.1, R20.1, U7.12 (IN+1)
unnamed: C34.1, R27.1, U7.15 (IN+2)
unnamed: C35.1, R32.1, U7.2 (IN+3)
unnamed: C32.2, R21.1, U7.11 (IN-1)
unnamed: C34.2, R29.1, U7.14 (IN-2)
unnamed: C35.2, R36.1, U7.1 (IN-3)

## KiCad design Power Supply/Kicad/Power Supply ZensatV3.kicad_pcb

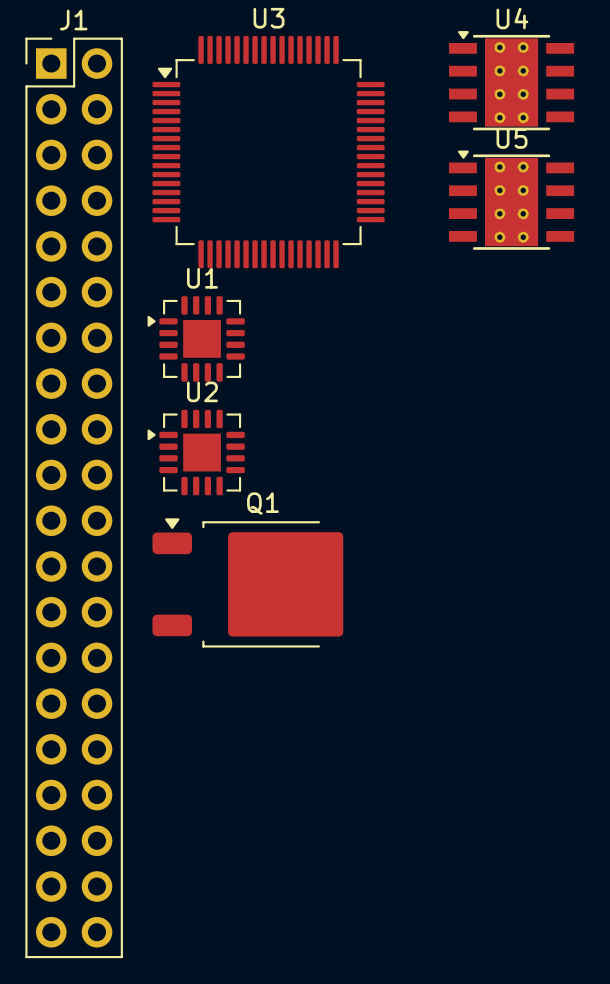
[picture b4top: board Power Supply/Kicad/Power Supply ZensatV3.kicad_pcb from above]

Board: 2 copper layers, 7 parts (0 on the bottom side), 6 nets, no tracks yet.

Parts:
J1: ZenBus; PinHeader_2x20_P2.54mm_Vertical
Q1: QM6006D; TO-252-2
U1, U2: INA3221; Texas_RGV0016A_VQFN-16-1EP_4x4mm_P0.65mm_EP2.1x2.1mm
U3: STM32L476RGTx; LQFP-64_10x10mm_P0.5mm
U4, U5: LMR33640DDDA; Texas_HSOP-8-1EP_3.9x4.9mm_P1.27mm_ThermalVias

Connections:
/3V3: J1.11, J1.12
/5V: J1.9, J1.10
/BAT+: J1.5, J1.6
GND: J1.1, J1.2, J1.3, J1.4, U1.3 (GND_3), U2.3 (GND_3), U3.12 (VSSA), U3.18 (VSS), U3.31 (VSS), U3.47 (VSS), U3.63 (VSS)
unnamed: U4.1 (GND), U4.9 (GND)
unnamed: U5.1 (GND), U5.9 (GND)

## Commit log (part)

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2026-06-28 Rename READMEold.md to README.md
2026-06-28 Add README.md file
